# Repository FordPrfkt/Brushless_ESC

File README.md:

# Brushless_ESC
Brushless Controller
Controller for Brushless Motors up to 20A

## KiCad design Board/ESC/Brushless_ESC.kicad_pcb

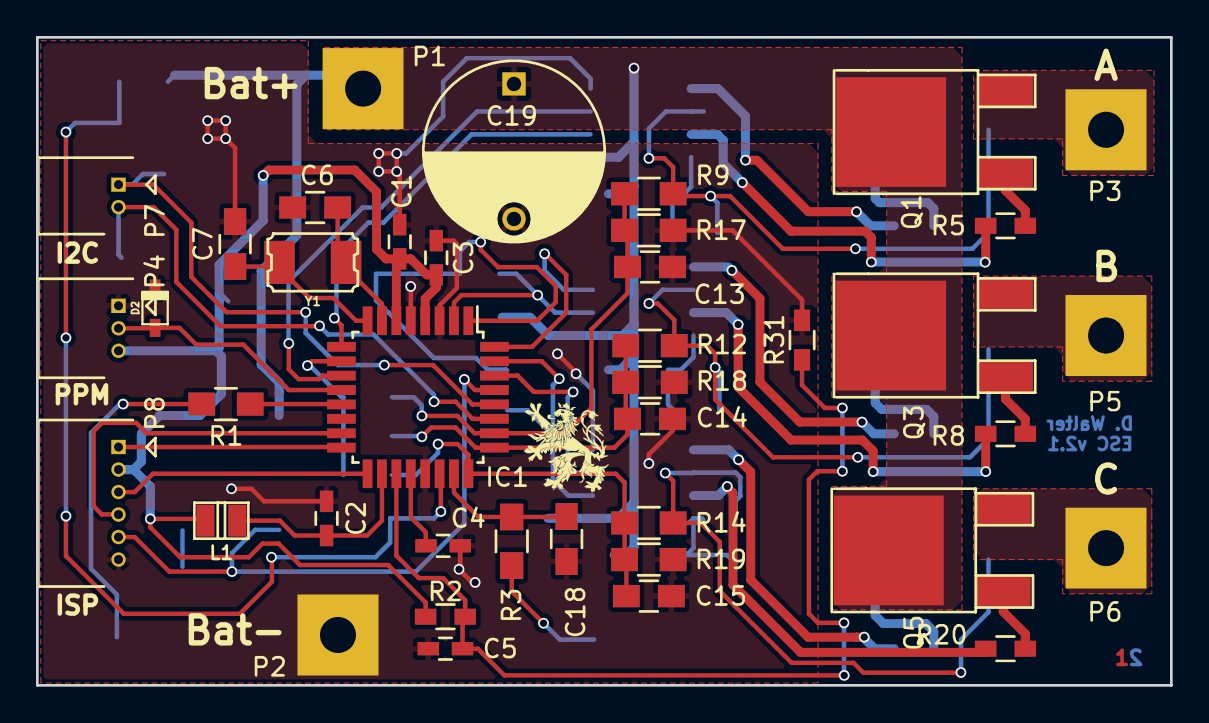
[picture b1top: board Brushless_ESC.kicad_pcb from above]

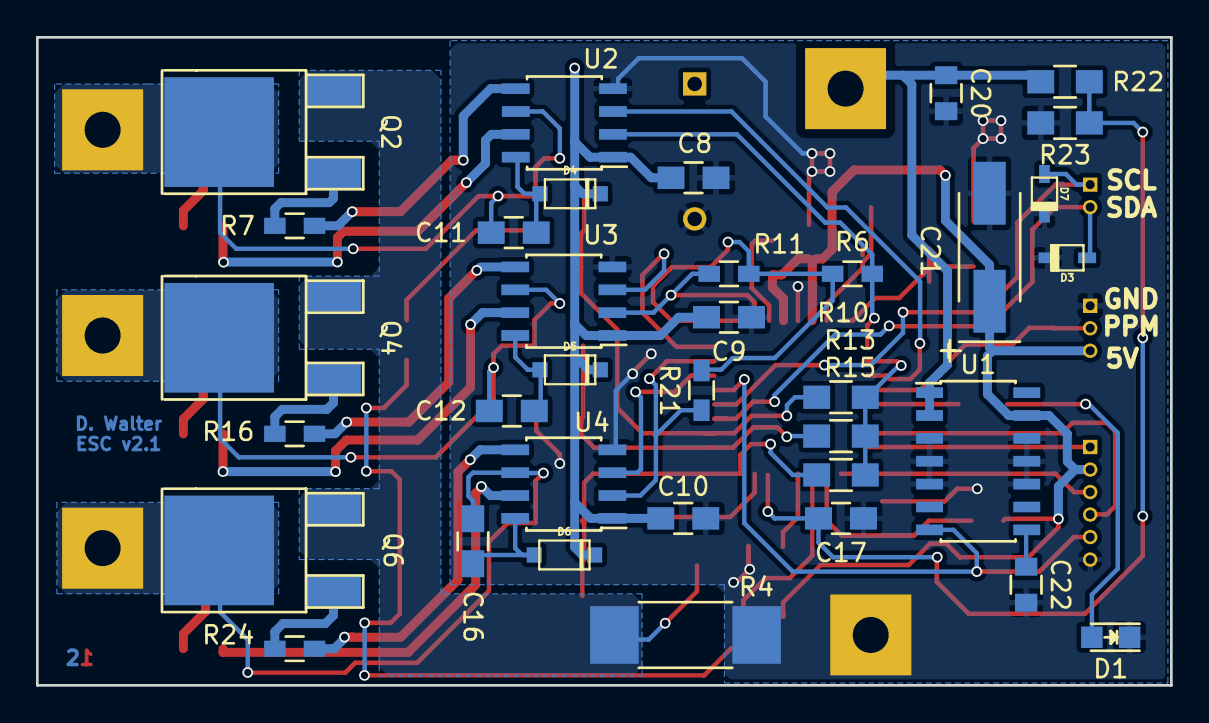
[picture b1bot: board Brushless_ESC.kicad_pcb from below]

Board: 2 copper layers, 63.0 x 36.0 mm, 76 parts (35 on the bottom side), 50 nets.

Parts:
C1, C2, C3, C4, C5: 100nF; C_0603_HandSoldering
C6, C7: 8pF; C_0805_HandSoldering
C8, C9, C10, C13, C14, C15, C17, C18: 100nF; C_0805_HandSoldering
C11, C12, C16: 220nF; C_0805_HandSoldering
C19: 1000µF; C_Radial_D10_L20_P7.5
C20: 470nF; C_0805
C21: 22µF; TantalC_SizeC_EIA-6032_HandSoldering
C22: 100nF; C_0805
D1: LED; LED_0805
D2, D3, D7: ZENER; sod323
D4, D5, D6: BAS21; sod123
IC1: ATMEGA88PA-A; TQFP-32_7x7mm_Pitch0.8mm
L1: 10µH; inductor_smd_0805
P1: Battery+; SolderWirePad_single_2mmDrill
P2, P2#2: Battery-; SolderWirePad_single_2mmDrill
P3: Coil_A; SolderWirePad_single_2mmDrill
P4: PPM; Molex_PicoBlade_53048-0310
P5: Coil_B; SolderWirePad_single_2mmDrill
P6: Coil_C; SolderWirePad_single_2mmDrill
P7: I2C; Molex_PicoBlade_53048-0210
P8: ISP; Molex_PicoBlade_53048-0610
Q1, Q2, Q3, Q4, Q5, Q6: IRL7843; TO-252-2Lead
R1: 220R; R_0805_HandSoldering
R2: 1k5; R_0603_HandSoldering
R3: 680R; R_0805_HandSoldering
R4: 0R02/5W; R_2512_HandSoldering
R5, R7, R8, R16, R20, R24: 47R; R_0603_HandSoldering
R6, R11, R21: 1k; R_0603_HandSoldering
R9, R10, R12, R13, R14, R15, R17, R18, R19: 4k7; R_0805_HandSoldering
R22: 1k5; R_0805_HandSoldering
R23: 470R; R_0805_HandSoldering
R31: 470R; R_0603_HandSoldering
U1: TLE4267; SOIC-14_3.9x8.7mm_Pitch1.27mm
U2, U3, U4: IR2104; SOIC-8_3.9x4.9mm_Pitch1.27mm
Y1: 20Mhz; crystal_smd_5x3.2mm

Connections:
+5V: C1.1, C3.1, C21.1, IC1.4, IC1.6, L1.2, P4.3, P8.2, R2.2, U1.13
+BATT: C8.1, C9.1, C10.1, C19.1, C20.1, D4.2, D5.2, D6.2, P1.1, Q1.2, Q3.2, Q5.2, R22.2, U1.1, U1.2, U2.1, U3.1, U4.1
/Controller//SD_A: IC1.11, U2.3
/Controller//SD_B: IC1.32, U3.3
/Controller//SD_C: IC1.30, U4.3
/Controller/BEMF_A: C13.1, IC1.26, R9.1, R10.2, R17.2
/Controller/BEMF_B: C14.1, IC1.25, R12.1, R13.2, R18.2
/Controller/BEMF_C: C15.1, IC1.24, R14.1, R15.2, R19.2
/Controller/BEMF_Center: IC1.10, R10.1, R13.1, R15.1
/Controller/BatCurrent+: C18.1, IC1.23, R3.2
/Controller/IN_A: IC1.9, R6.1, U2.2
/Controller/IN_B: IC1.2, R11.1, U3.2
/Controller/IN_C: IC1.31, R21.1, U4.2
/Controller/PPM: D2.1, IC1.12, P4.2
/Controller/PWM: IC1.1, R6.2, R11.2, R21.2
/Controller/Reset: IC1.29, P8.5, U1.7
/Controller/SCL: D7.1, IC1.28, P7.1
/Controller/SDA: D3.1, IC1.27, P7.2
/Controller/T_Sense: C5.1, IC1.19, R2.1, R31.2
/Controller/V_Bat: C17.1, IC1.22, R22.1, R23.2
/Power/Coil_A: C11.2, P3.1, Q1.3, Q2.2, R9.2, U2.6
/Power/Coil_B: C12.2, P5.1, Q3.3, Q4.2, R12.2, U3.6
/Power/Coil_C: C16.2, P6.1, Q5.3, Q6.2, R14.2, U4.6
GND: C1.2, C2.2, C3.2, C4.2, C5.2, C6.2, C7.1, C8.2, C9.2, C10.2, C13.2, C14.2, C15.2, C17.2, C18.2, C19.2, C20.2, C21.2, C22.2, D1.1, D2.2, D3.2, D7.2, IC1.3, IC1.5, IC1.21, P2#2.1, P4.1, P8.6, R4.1, R17.1, R18.1, R19.1, R23.1, R31.1, U1.3, U1.4, U1.5, U1.10, U1.11, U1.12, U2.4, U3.4, U4.4
unnamed: C2.1, IC1.18, L1.1
unnamed: C4.1, IC1.20
unnamed: C6.1, IC1.7, Y1.1
unnamed: C7.2, IC1.8, Y1.2
unnamed: C11.1, D4.1, U2.8
unnamed: C12.1, D5.1, U3.8
unnamed: C16.1, D6.1, U4.8
unnamed: C22.1, U1.8
unnamed: D1.2, R1.1
unnamed: IC1.13, R1.2
unnamed: IC1.15, P8.4
unnamed: IC1.16, P8.1
unnamed: IC1.17, P8.3
unnamed: Q1.1, R5.1
unnamed: Q2.1, R7.1
unnamed: Q2.3, Q4.3, Q6.3, R3.1, R4.2
unnamed: Q3.1, R8.1
unnamed: Q4.1, R16.1
unnamed: Q5.1, R20.1
unnamed: Q6.1, R24.1
unnamed: R5.2, U2.7
unnamed: R7.2, U2.5
unnamed: R8.2, U3.7
unnamed: R16.2, U3.5
unnamed: R20.2, U4.7
unnamed: R24.2, U4.5

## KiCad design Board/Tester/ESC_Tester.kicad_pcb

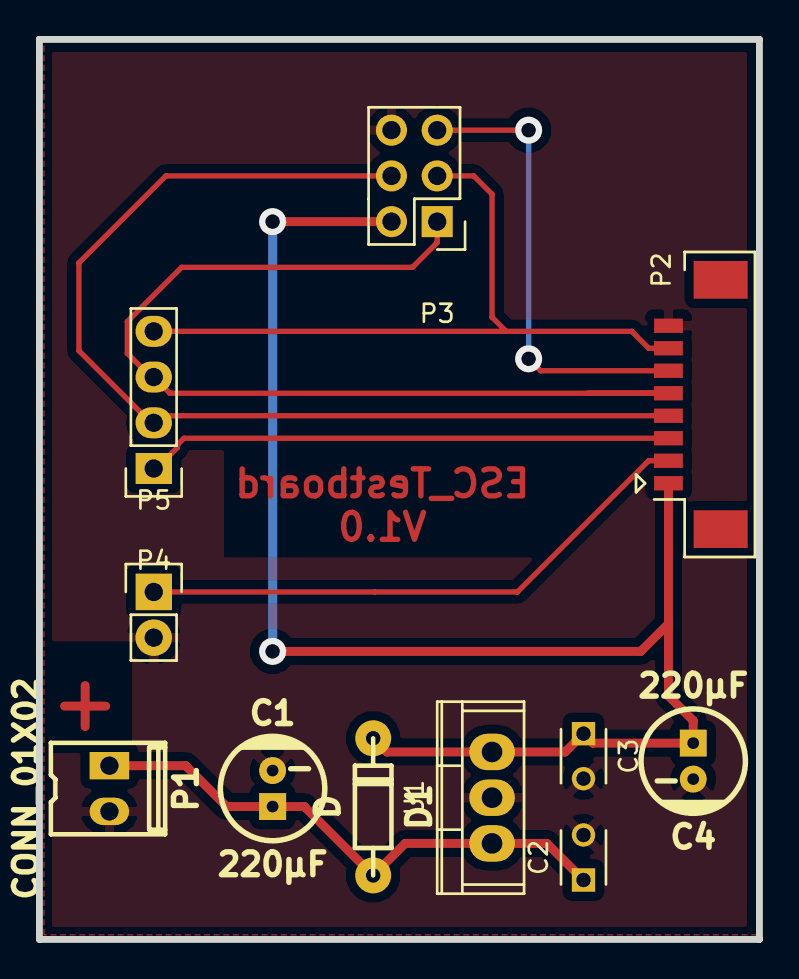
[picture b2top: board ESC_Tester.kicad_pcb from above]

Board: 2 copper layers, 40.0 x 50.0 mm, 11 parts (0 on the bottom side), 9 nets.

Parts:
C1, C4: 220µF; CP_5x5mm
C2, C3: 100nF; C_Disc_D3_P2.5
D1: D; diode_do35
P1: CONN_01X02; kk100_22-23-2021
P2: CONN_BLDC; Connector_Molex_PicoBlade_53261-0871
P3: CONN_ISP; Pin_Header_Straight_2x03
P4: CONN_SPI; Pin_Header_Straight_1x04
P5: CONN_PPM; Pin_Header_Straight_1x02
U1: LM7805CT; TO-220

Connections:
+5V: C3.1, C4.1, D1.2, P2.1, P3.2, U1.3
/MISO: P2.5, P3.1, P4.3
/MOSI: P2.4, P3.4, P4.2
/PPM: P2.2, P5.1
/Reset: P2.6, P3.5
/SCK: P2.7, P3.3, P4.4
/SS: P2.3, P4.1
GND: C1.2, C2.2, C3.2, C4.2, P1.2, P2.8, P3.6, P5.2, U1.2
unnamed: C1.1, C2.1, D1.1, P1.1, U1.1

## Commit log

2015-09-26 Added GIT Config for Atmmel Studio
2015-09-26 Layout Fehler (LED an ADC7) behoben
2015-09-26 Added PID Controller Added SPI Work in Progress on Commutation
2015-09-26 Updated gitignore
2015-09-26 Testboard erstellt
2015-09-27 Work in Progress at the Firmware, added 3D Picture of the Board
2015-09-27 Minor Layout changes
2015-10-11 Work in Progress
2015-10-11 Nicht benötigte Datei gelöscht
2015-11-01 BOM erzeugt, Testerboard layout
2015-11-07 Umrechnung Ticks in ns, Strombegrenzung, Drehzahlberechnung, ADC Referenzumschaltung
2016-03-27 Repaired Repository, Fixed wrong footprint of FETs
2016-03-27 Temperaturmessung hinzugefügt
2016-03-29 Layoutänderung
2016-03-29 Soundausgabe
2016-04-03 BEC eingebaut, Interface auf I2C umgestellt, Zenderdioden
2016-04-09 Layoutänderungen
2016-04-11 Layoutoptimierung
2016-04-16 Final Layout
2016-04-28 Version zur Fertigung
2016-05-02 Fixed 3d Models
2016-05-02 Added Pictures
2016-05-02 Removed Testerboard
2016-05-08 I2C Interface implementierung begonnen
2016-06-25 Some more Layout changes, Layout now Final
2016-06-30 Added I2C Slave Handler and Driver
2016-07-02 Implemented TWI Handler
2016-07-02 Added TWI Files
2016-07-02 Removed unneccessary files
2016-07-02 Renamed folder
